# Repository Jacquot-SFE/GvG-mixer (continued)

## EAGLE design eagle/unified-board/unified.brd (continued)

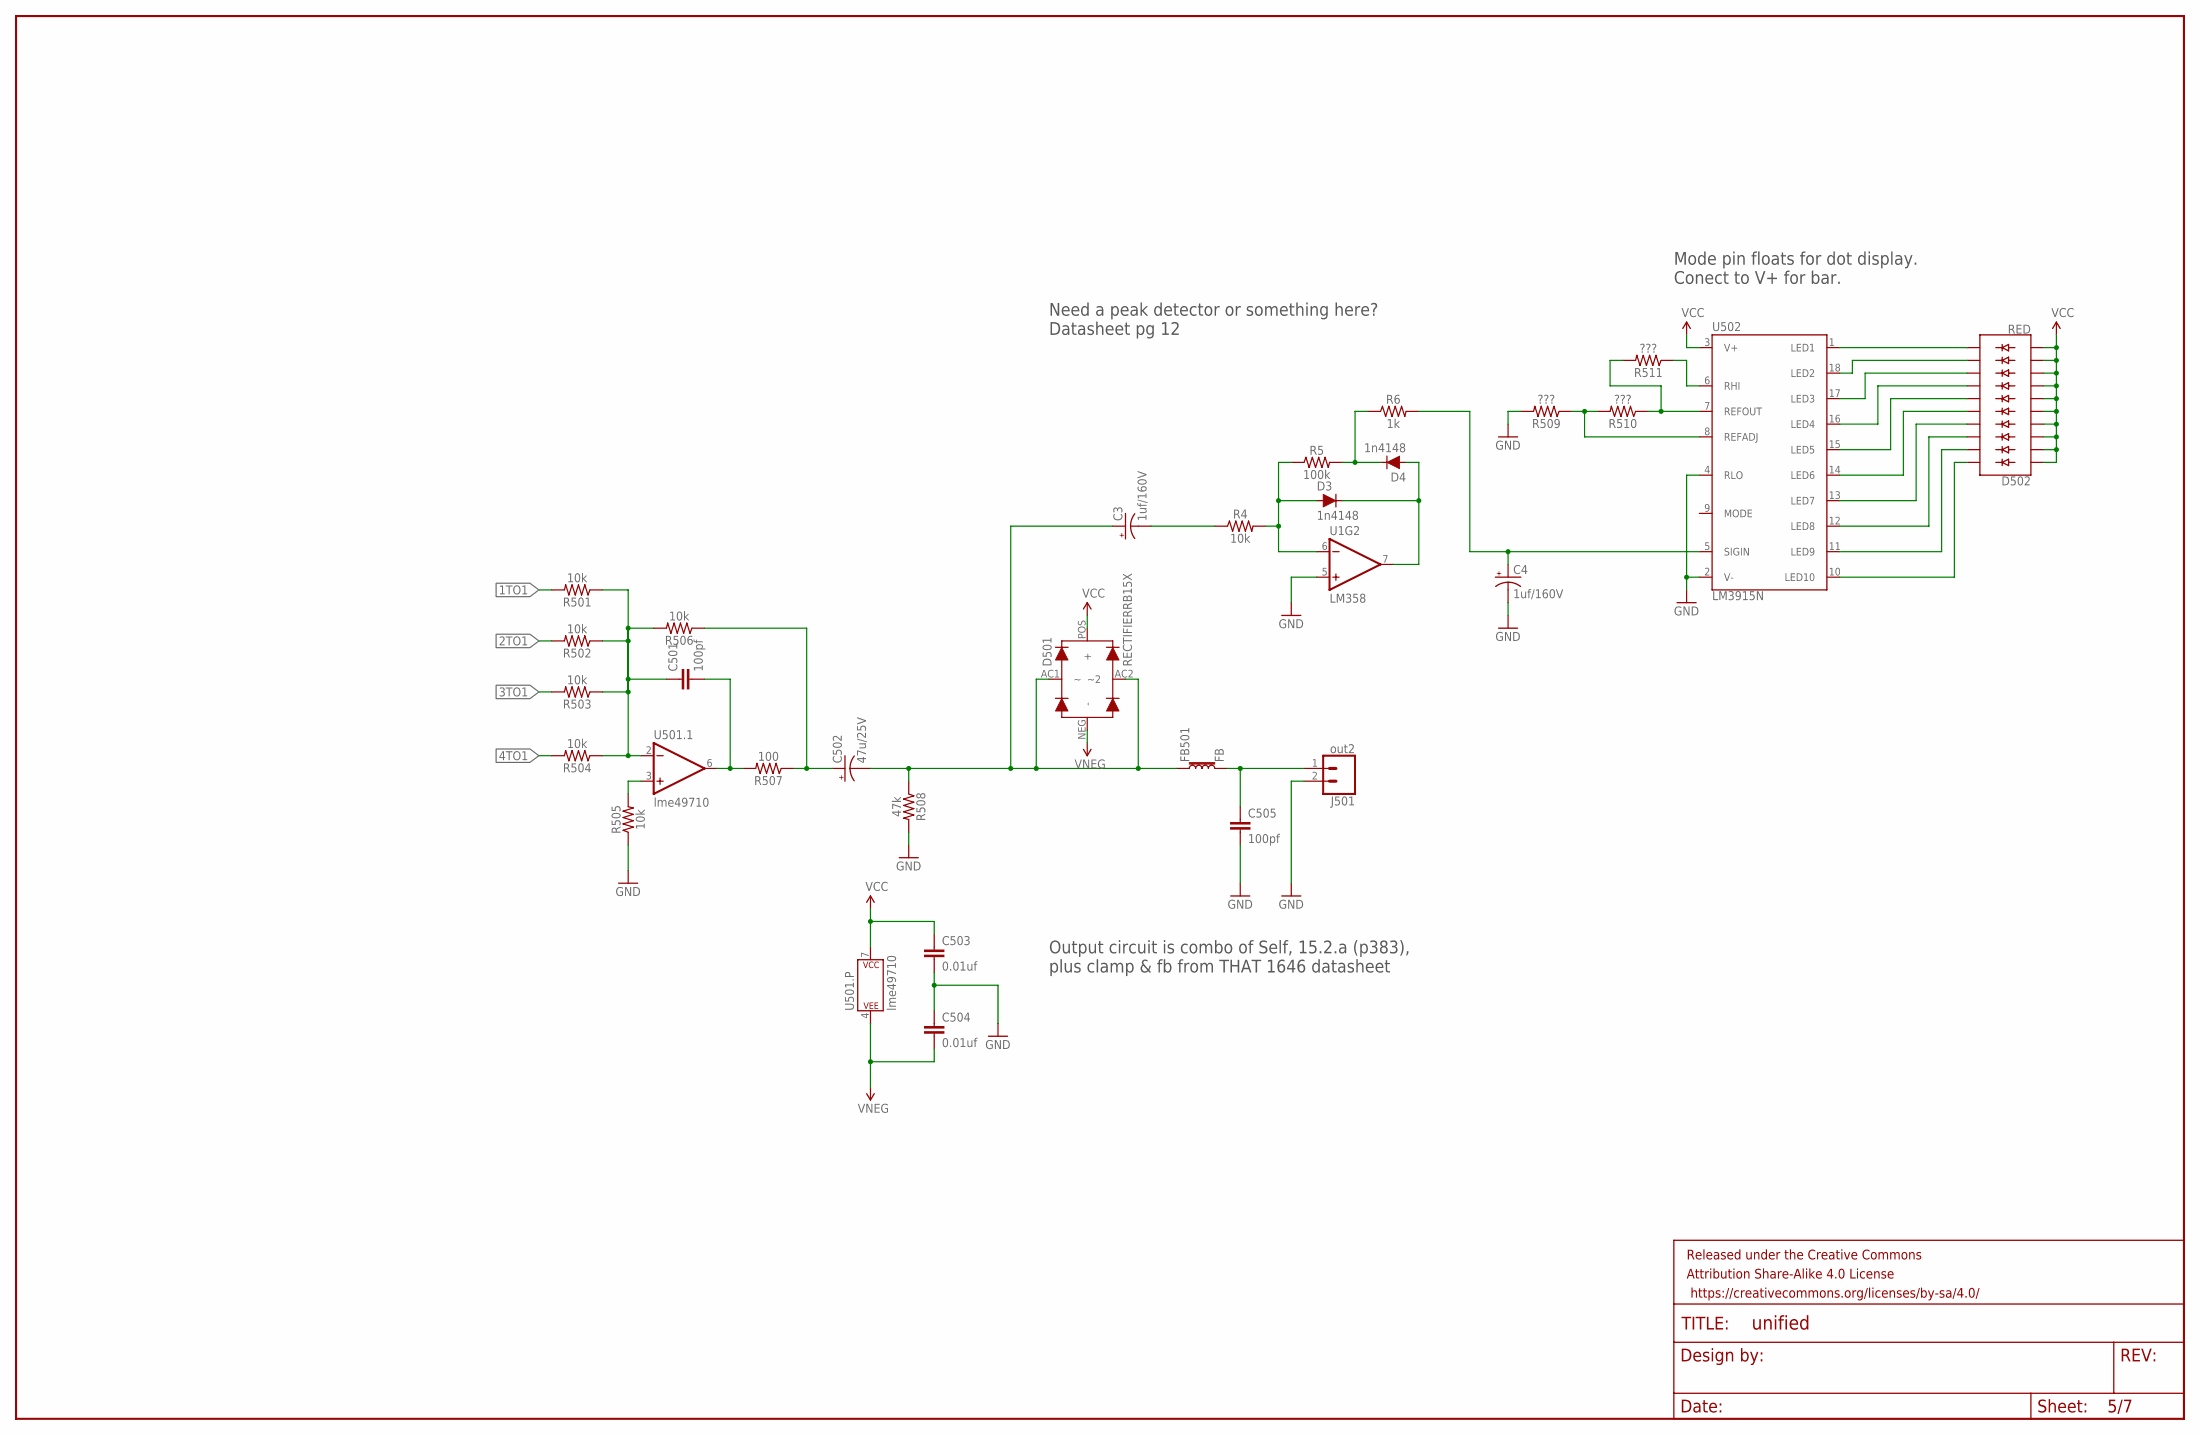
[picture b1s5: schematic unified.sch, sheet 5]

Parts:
C3, C4: 1uf/160V; CAP-PANA-2.5LS-6DIAM
C501, C505: 100pf; CAP-KEMET-GM-2.54LS
C502: 47u/25V; CAP-PANA-2LS-5DIAM
C503, C504: 0.01uf; WIMA-MKS2-2.5X7.2
D3, D4: 1n4148; DIODE-1N4148
D501: RECTIFIERRB15X; SM-RECTIFIER
D502: RED; LED_BARGRAPH_10
FB501: FB; BEAD
FRAME501: FRAME-LEDGER; CREATIVE_COMMONS
J501: out2; 1X02_LOCK_LONGPADS
R4, R501, R502, R503, R504, R505, R506: 10k; AXIAL-0.3
R5: 100k; AXIAL-0.3
R6: 1k; AXIAL-0.3
R507: 100; AXIAL-0.3
R508: 47k; AXIAL-0.3
R509, R510, R511: ???; AXIAL-0.3
U1: LM358; DIP08
U501: lme49710; DIP08-KIT
U502: LM3915N; DIL18

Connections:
1TO1: R501.P$2 (2); also elsewhere on the board
2TO1: R502.P$2 (2); also elsewhere on the board
3TO1: R503.P$2 (2); also elsewhere on the board
4TO1: R504.P$2 (2); also elsewhere on the board
GND: C4.NEG (-), C503.P$2 (2), C504.P$1 (1), C505.P$2 (2), J501.2, R505.P$1 (1), R508.P$2 (2), R509.P$2 (2), U1.5 (+IN), U502.2 (V-), U502.4 (RLO); also elsewhere on the board
HIGHEST1: D502.20 (C), U502.10 (LED10)
LOWEST1: D502.11 (C9), U502.1 (LED1)
unnamed: D3.A, R4.P$2 (2), R5.P$1 (1), U1.6 (-IN)
unnamed: D3.C, D4.A, U1.7 (OUT)
unnamed: D4.C, R5.P$2 (2), R6.P$1 (1)
unnamed: C3.NEG (-), R4.P$1 (1)
unnamed: C4.POS (+), R6.P$2 (2), U502.5 (SIGIN)
unnamed: R505.P$2 (2), U501.3 (+IN)
unnamed: C501.P$1 (1), R501.P$1 (1), R502.P$1 (1), R503.P$1 (1), R504.P$1 (1), R506.P$2 (2), U501.2 (-IN)
unnamed: C505.P$1 (1), FB501.P$2 (2), J501.1
unnamed: C3.POS (+), C502.NEG (-), D501.AC1, D501.AC2 (~2), FB501.P$1 (1), R508.P$1 (1)
unnamed: D502.12 (C8), U502.18 (LED2)
unnamed: D502.13 (C7), U502.17 (LED3)
unnamed: D502.14 (C6), U502.16 (LED4)
unnamed: D502.15 (C5), U502.15 (LED5)
unnamed: D502.16 (C4), U502.14 (LED6)
unnamed: D502.17 (C3), U502.13 (LED7)
unnamed: D502.18 (C2), U502.12 (LED8)
unnamed: D502.19 (C1), U502.11 (LED9)
unnamed: R510.P$1 (1), R511.P$2 (2), U502.7 (REFOUT)
unnamed: R509.P$1 (1), R510.P$2 (2), U502.8 (REFADJ)
unnamed: C501.P$2 (2), R507.P$2 (2), U501.6 (OUT)
unnamed: C502.POS (+), R506.P$1 (1), R507.P$1 (1)
unnamed: R511.P$1 (1), U502.6 (RHI)
VCC: C503.P$1 (1), D501.POS (+), D502.1 (A), D502.2 (A1), D502.3 (A2), D502.4 (A3), D502.5 (A4), D502.6 (A5), D502.7 (A6), D502.8 (A7), D502.9 (A8), D502.10 (A9), U501.7 (P$V+), U502.3 (V+); also elsewhere on the board
VNEG: C504.P$2 (2), D501.NEG (-), U501.4 (P$V-); also elsewhere on the board

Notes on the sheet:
Need a peak detector or something here? Datasheet pg 12
Mode pin floats for dot display. Conect to V+ for bar.
Output circuit is combo of Self, 15.2.a (p383), plus clamp & fb from THAT 1646 datasheet

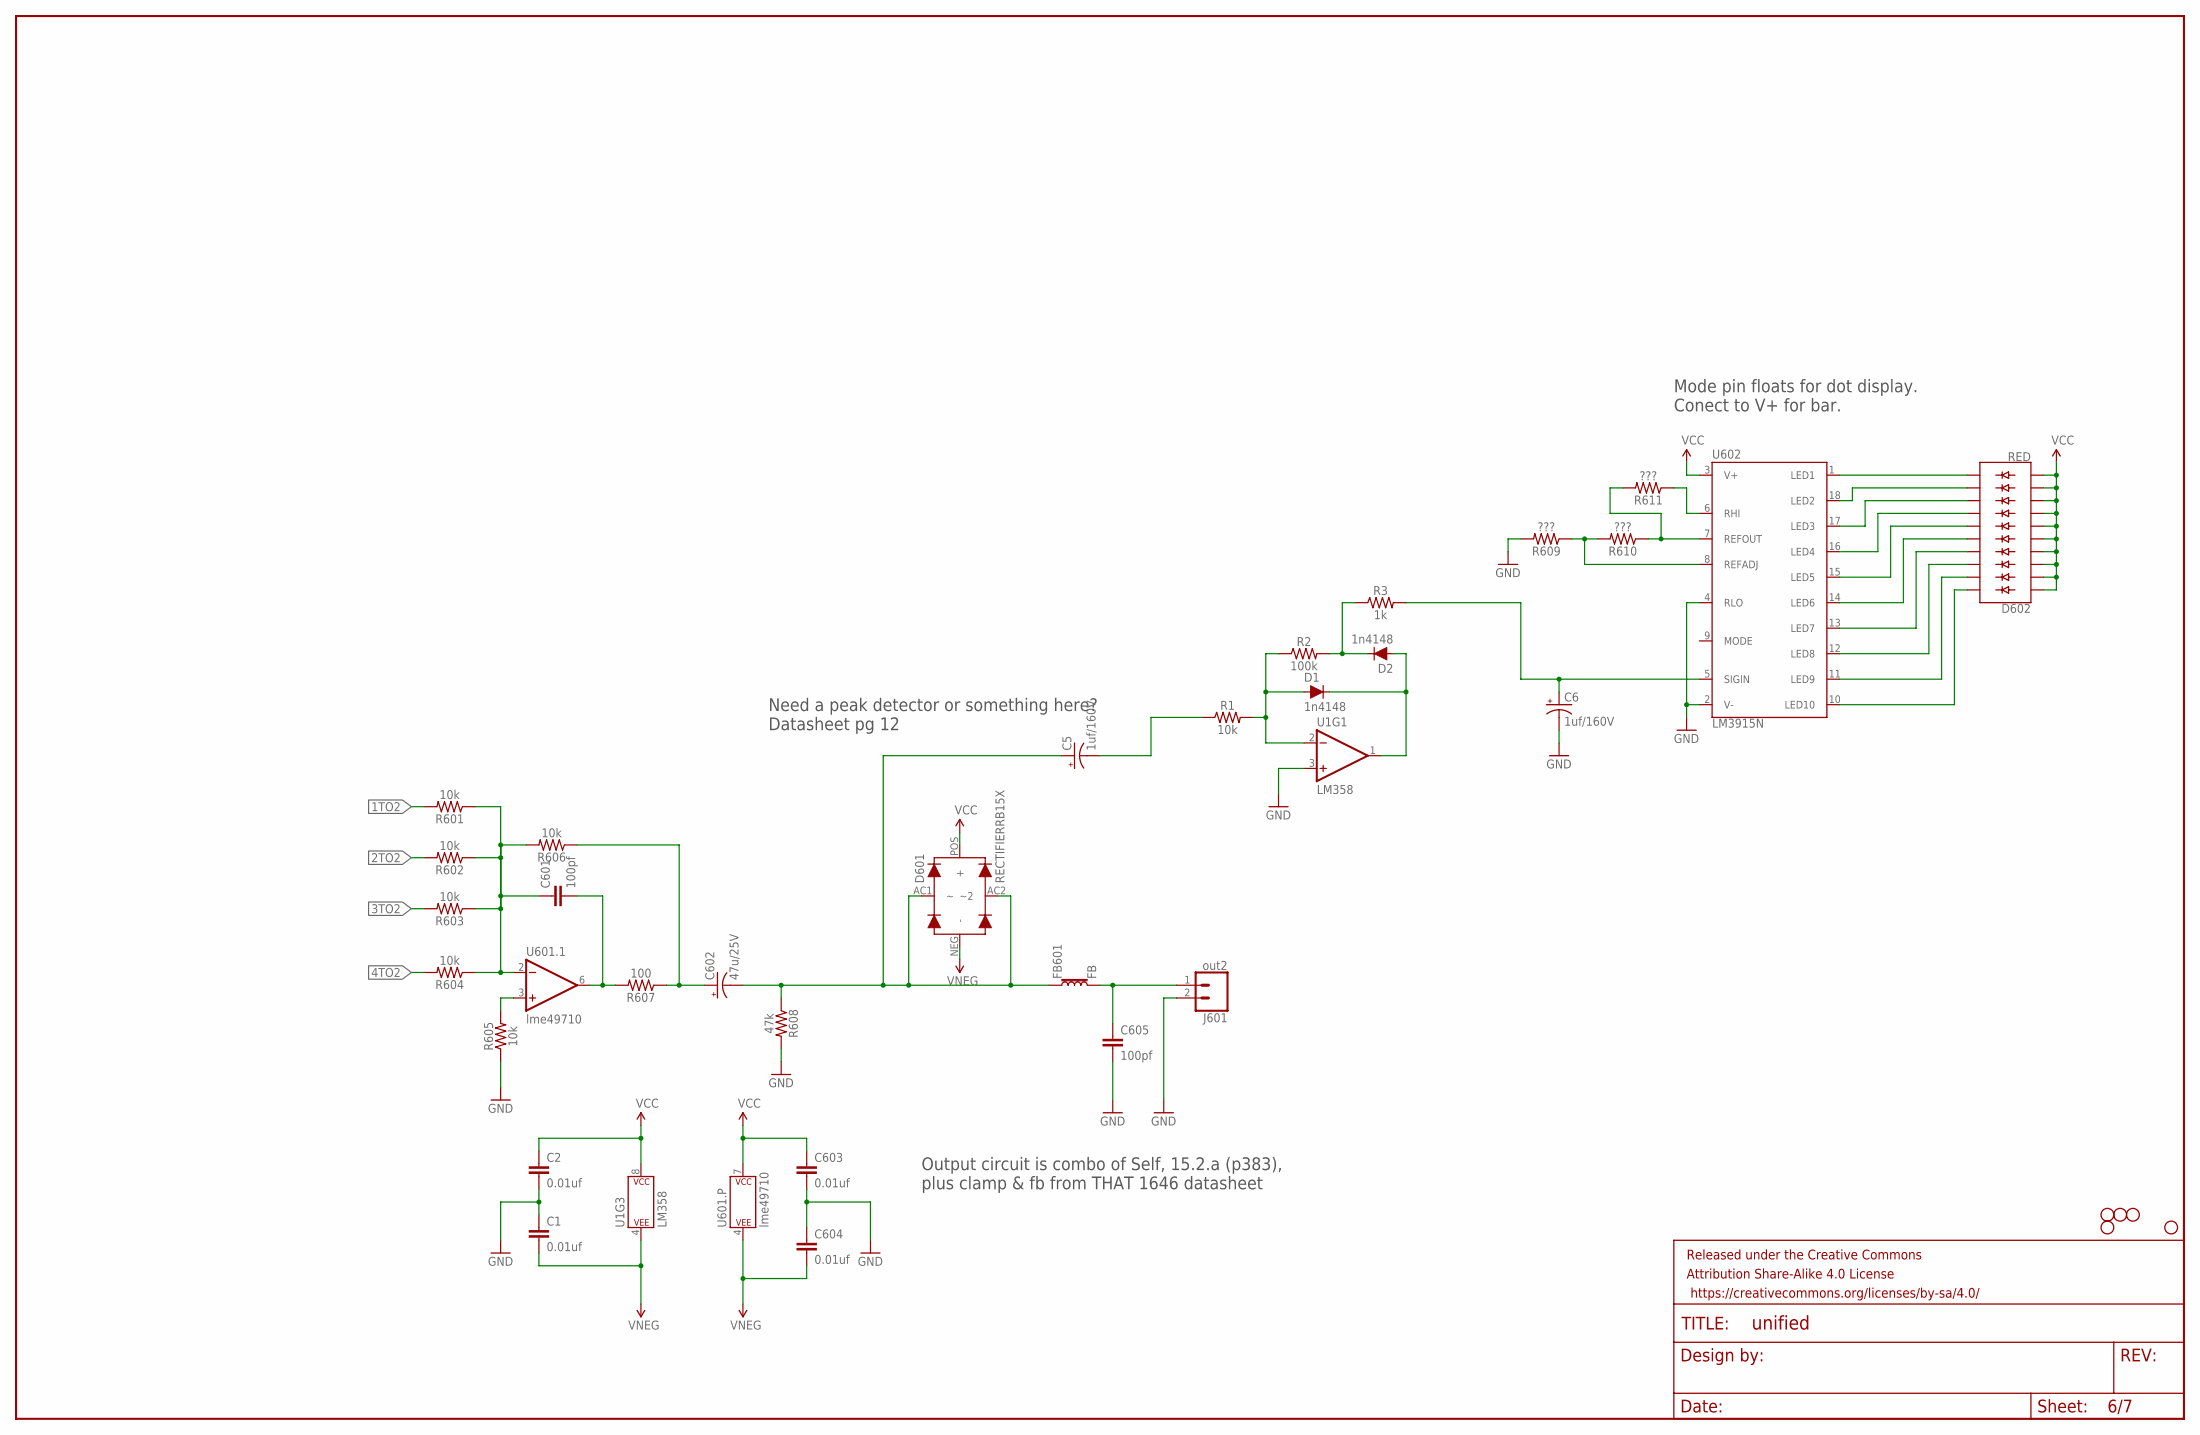
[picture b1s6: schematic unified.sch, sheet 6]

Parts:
C1, C2, C603, C604: 0.01uf; WIMA-MKS2-2.5X7.2
C5, C6: 1uf/160V; CAP-PANA-2.5LS-6DIAM
C601, C605: 100pf; CAP-KEMET-GM-2.54LS
C602: 47u/25V; CAP-PANA-2LS-5DIAM
D1, D2: 1n4148; DIODE-1N4148
D601: RECTIFIERRB15X; SM-RECTIFIER
D602: RED; LED_BARGRAPH_10
FB601: FB; BEAD
FRAME601: FRAME-LEDGER; CREATIVE_COMMONS
H601, H602, H603, H605, H612: STAND-OFF
J601: out2; 1X02_LOCK_LONGPADS
R1, R601, R602, R603, R604, R605, R606: 10k; AXIAL-0.3
R2: 100k; AXIAL-0.3
R3: 1k; AXIAL-0.3
R607: 100; AXIAL-0.3
R608: 47k; AXIAL-0.3
R609, R610, R611: ???; AXIAL-0.3
U1: LM358; DIP08
U601: lme49710; DIP08-KIT
U602: LM3915N; DIL18

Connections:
1TO2: R601.P$2 (2); also elsewhere on the board
2TO2: R602.P$2 (2); also elsewhere on the board
3TO2: R603.P$2 (2); also elsewhere on the board
4TO2: R604.P$2 (2); also elsewhere on the board
GND: C1.P$1 (1), C2.P$2 (2), C6.NEG (-), C603.P$2 (2), C604.P$1 (1), C605.P$2 (2), J601.2, R605.P$1 (1), R608.P$2 (2), R609.P$2 (2), U1.3 (+IN), U602.2 (V-), U602.4 (RLO); also elsewhere on the board
HIGHEST: D602.20 (C), U602.10 (LED10)
LOWEST: D602.11 (C9), U602.1 (LED1)
unnamed: D1.A, R1.P$2 (2), R2.P$1 (1), U1.2 (-IN)
unnamed: C605.P$1 (1), FB601.P$2 (2), J601.1
unnamed: D1.C, D2.A, U1.1 (OUT)
unnamed: C5.POS (+), C602.NEG (-), D601.AC1, D601.AC2 (~2), FB601.P$1 (1), R608.P$1 (1)
unnamed: C602.POS (+), R606.P$1 (1), R607.P$1 (1)
unnamed: R605.P$2 (2), U601.3 (+IN)
unnamed: C601.P$2 (2), R607.P$2 (2), U601.6 (OUT)
unnamed: C601.P$1 (1), R601.P$1 (1), R602.P$1 (1), R603.P$1 (1), R604.P$1 (1), R606.P$2 (2), U601.2 (-IN)
unnamed: D2.C, R2.P$2 (2), R3.P$1 (1)
unnamed: C6.POS (+), R3.P$2 (2), U602.5 (SIGIN)
unnamed: D602.12 (C8), U602.18 (LED2)
unnamed: D602.13 (C7), U602.17 (LED3)
unnamed: D602.14 (C6), U602.16 (LED4)
unnamed: D602.15 (C5), U602.15 (LED5)
unnamed: D602.16 (C4), U602.14 (LED6)
unnamed: D602.17 (C3), U602.13 (LED7)
unnamed: D602.18 (C2), U602.12 (LED8)
unnamed: D602.19 (C1), U602.11 (LED9)
unnamed: R610.P$1 (1), R611.P$2 (2), U602.7 (REFOUT)
unnamed: R609.P$1 (1), R610.P$2 (2), U602.8 (REFADJ)
unnamed: R611.P$1 (1), U602.6 (RHI)
unnamed: C5.NEG (-), R1.P$1 (1)
VCC: C2.P$1 (1), C603.P$1 (1), D601.POS (+), D602.1 (A), D602.2 (A1), D602.3 (A2), D602.4 (A3), D602.5 (A4), D602.6 (A5), D602.7 (A6), D602.8 (A7), D602.9 (A8), D602.10 (A9), U1.8 (P$V+), U601.7 (P$V+), U602.3 (V+); also elsewhere on the board
VNEG: C1.P$2 (2), C604.P$2 (2), D601.NEG (-), U1.4 (P$V-), U601.4 (P$V-); also elsewhere on the board

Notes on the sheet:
Need a peak detector or something here? Datasheet pg 12
Mode pin floats for dot display. Conect to V+ for bar.
Output circuit is combo of Self, 15.2.a (p383), plus clamp & fb from THAT 1646 datasheet

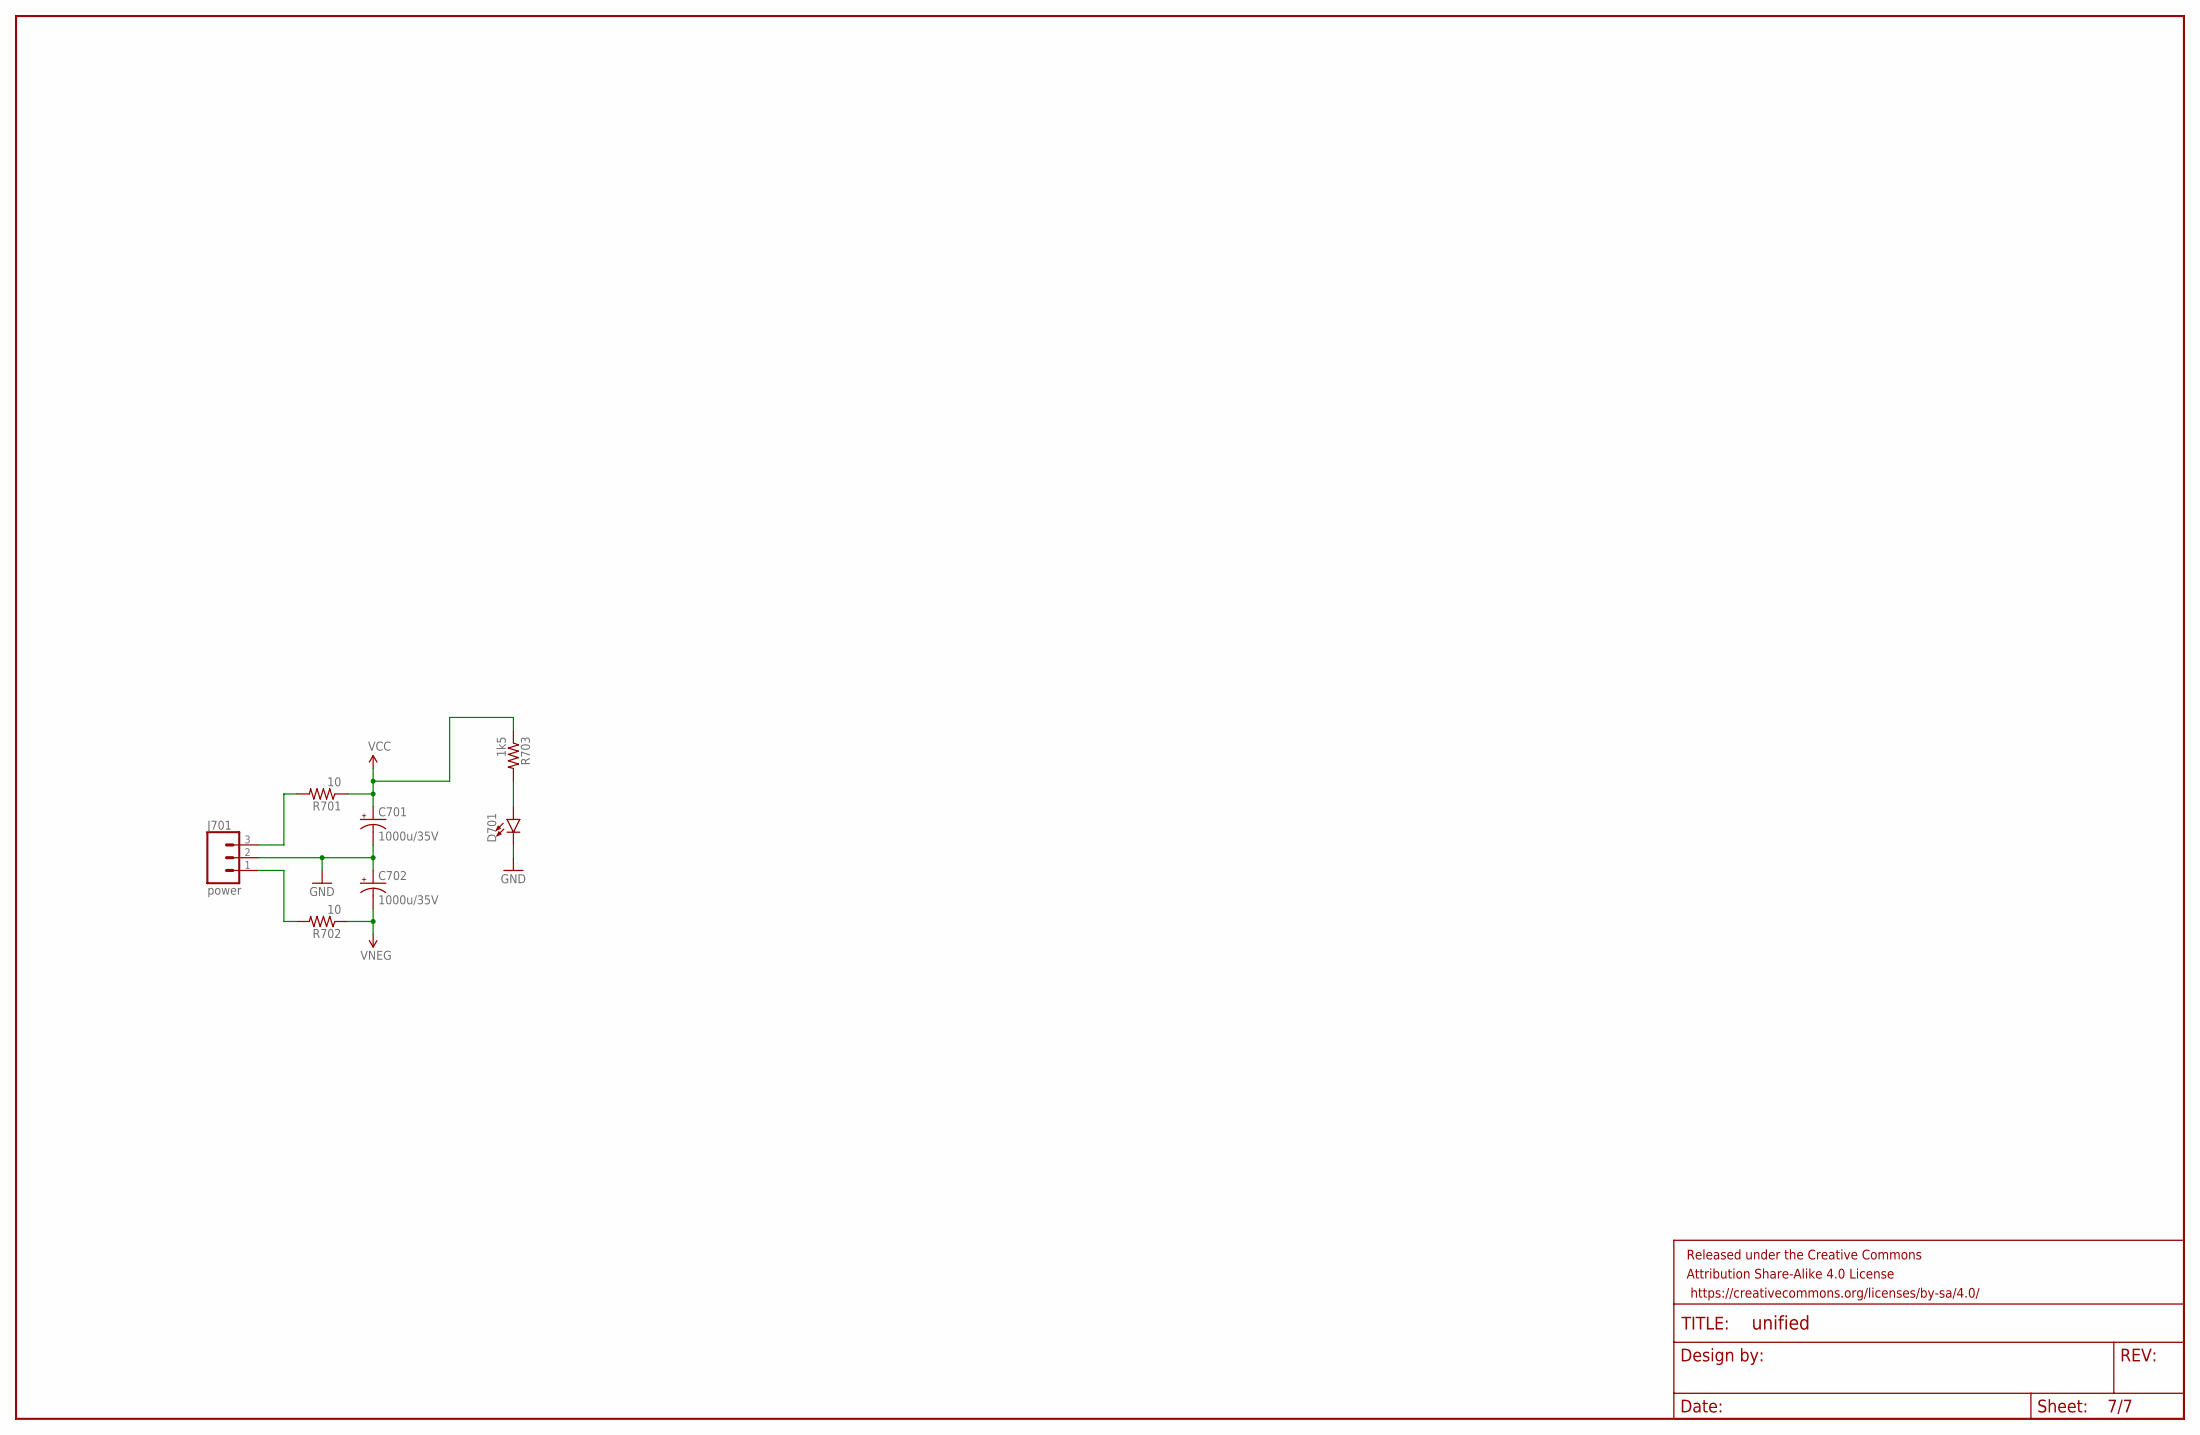
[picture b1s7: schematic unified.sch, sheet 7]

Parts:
C701, C702: 1000u/35V; CAP-PANA-5LS-12.5DIAM
D701: LED5MM; LED_5MM
FRAME701: FRAME-LEDGER; CREATIVE_COMMONS
J701: power; MOLEX-1X3_LOCK
R701, R702: 10; AXIAL-0.3
R703: 1k5; AXIAL-0.3

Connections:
GND: C701.NEG (-), C702.POS (+), D701.K (C), J701.2; also elsewhere on the board
unnamed: J701.1, R702.P$2 (2)
unnamed: J701.3, R701.P$2 (2)
unnamed: D701.A, R703.P$2 (2)
VCC: C701.POS (+), R701.P$1 (1), R703.P$1 (1); also elsewhere on the board
VNEG: C702.NEG (-), R702.P$1 (1); also elsewhere on the board

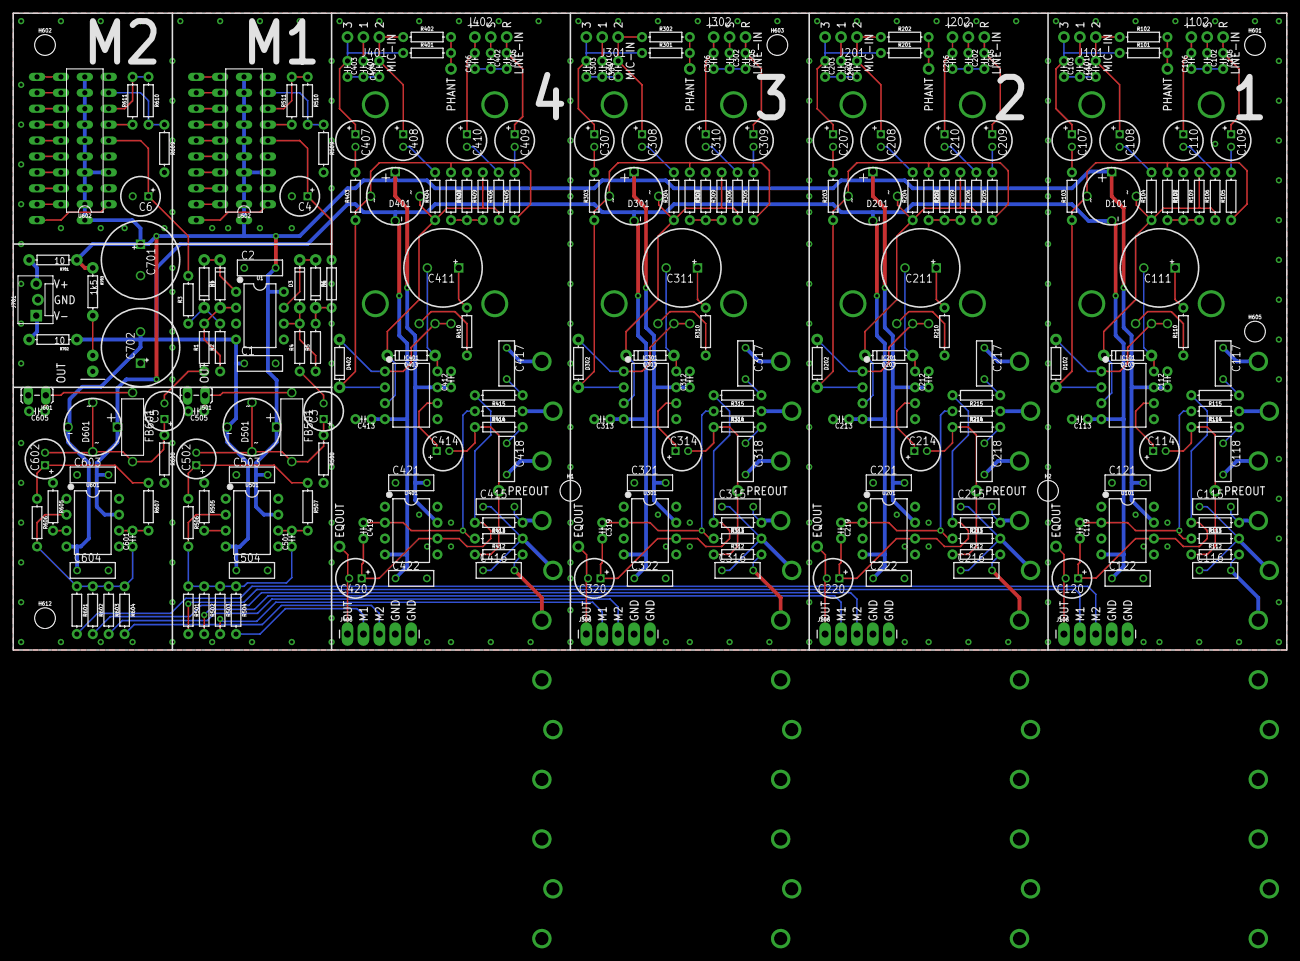
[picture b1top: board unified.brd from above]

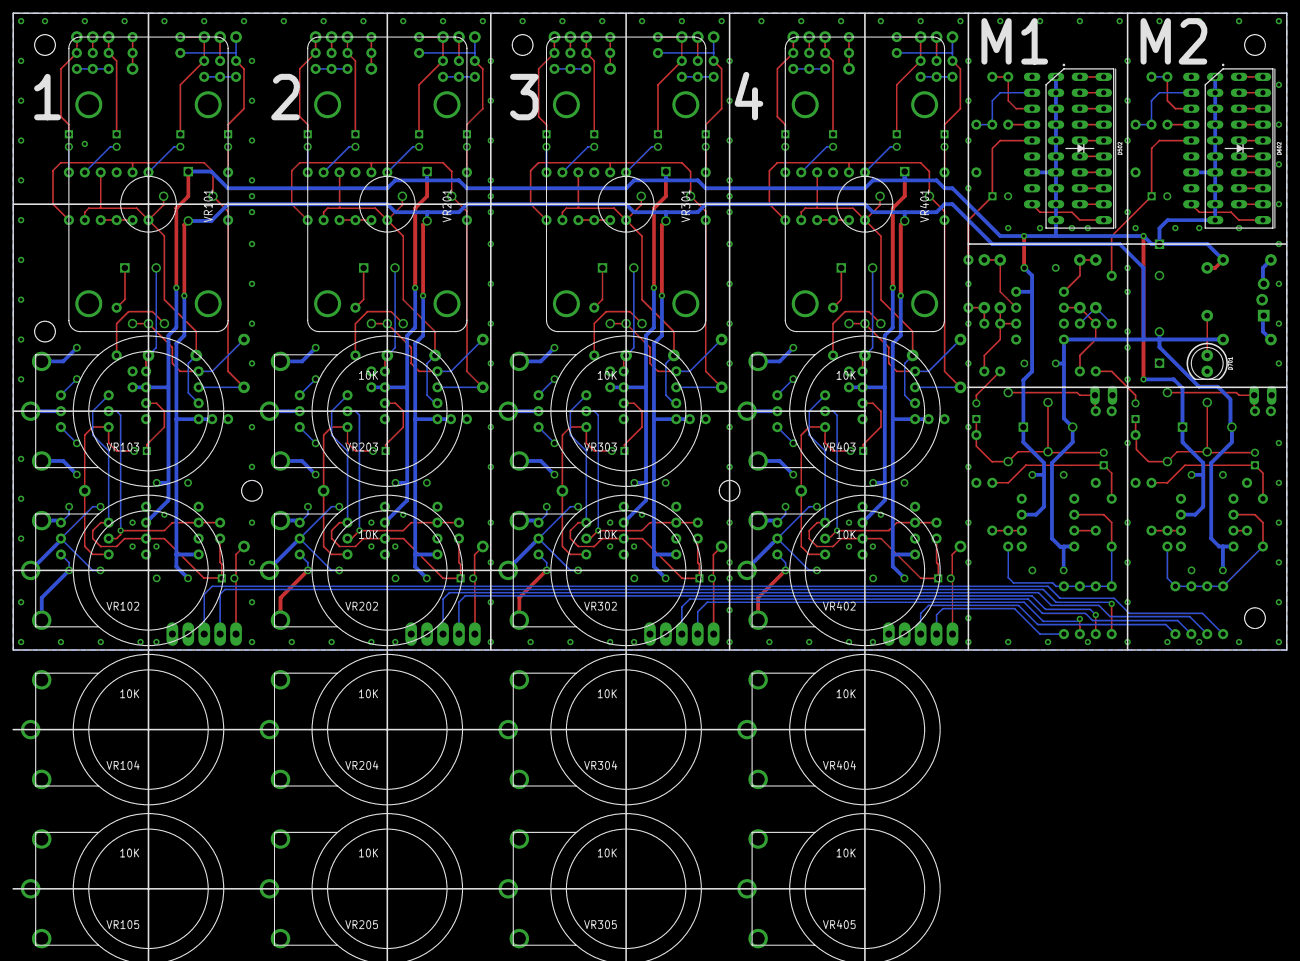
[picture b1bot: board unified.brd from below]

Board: 2 copper layers, 203.2 x 101.6 mm, 298 parts (23 on the bottom side), 194 nets.

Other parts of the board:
H1, H2: STAND-OFF

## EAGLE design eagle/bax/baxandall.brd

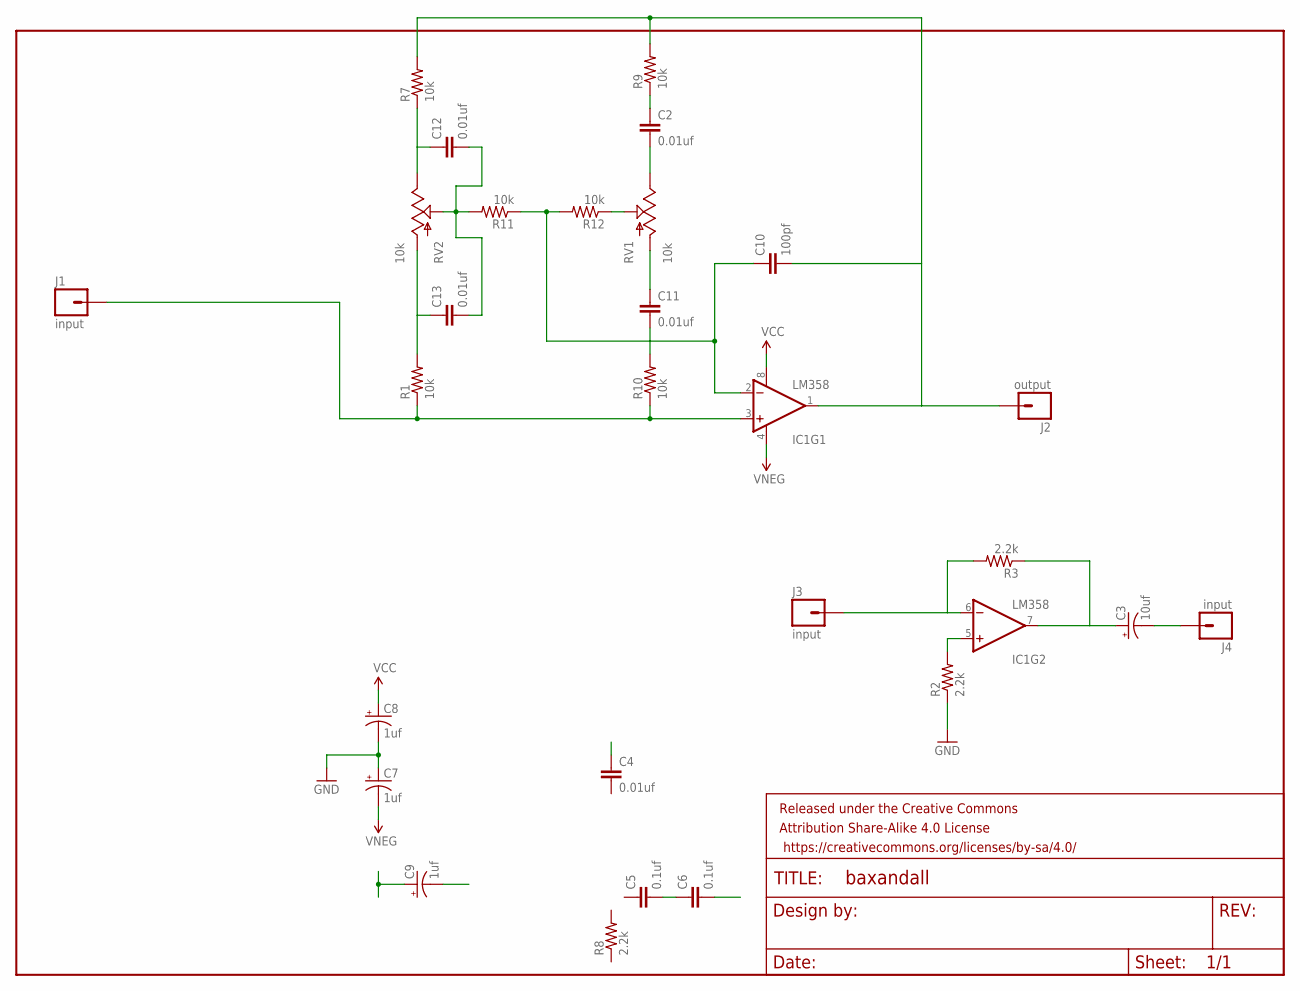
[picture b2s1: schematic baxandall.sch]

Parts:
C2, C4, C11, C12, C13: 0.01uf; CAP-PTH-SMALL
C3: 10uf; CPOL-RADIAL-10UF-25V
C5, C6: 0.1uf; CAP-PTH-SMALL
C7, C8, C9: 1uf; CPOL-RADIAL-10UF-25V
C10: 100pf; CAP-PTH-SMALL
FRAME1: FRAME-LETTER; CREATIVE_COMMONS
IC1: LM358; DIP08
J1, J3, J4: input; 1X01NS-KIT
J2: output; 1X01NS-KIT
R1, R7, R9, R10, R11, R12: 10k; AXIAL-0.3
R2, R3, R8: 2.2k; AXIAL-0.3
RV1, RV2: 10k; POT_ALPHA_RV16AF-20

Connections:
GND: C7.1 (+), C8.2 (-), R2.P$1 (1)
unnamed: C12.1, R7.P$1 (1), RV2.3 (E)
unnamed: C13.1, R1.P$2 (2), RV2.1 (A)
unnamed: C10.1, IC1.2 (-IN), R11.P$1 (1), R12.P$2 (2)
unnamed: C11.2, R10.P$2 (2)
unnamed: C10.2, IC1.1 (OUT), J2.1, R7.P$2 (2), R9.P$2 (2)
unnamed: IC1.5 (+IN), R2.P$2 (2)
unnamed: C3.1 (+), IC1.7 (OUT), R3.P$1 (1)
unnamed: R12.P$1 (1), RV1.2 (S)
unnamed: IC1.3 (+IN), J1.1, R1.P$1 (1), R10.P$1 (1)
unnamed: C11.1, RV1.1 (A)
unnamed: IC1.6 (-IN), J3.1, R3.P$2 (2)
unnamed: C3.2 (-), J4.1
unnamed: C12.2, C13.2, R11.P$2 (2), RV2.2 (S)
unnamed: C2.2, RV1.3 (E)
unnamed: C5.2, C6.1
unnamed: C2.1, R9.P$1 (1)
VCC: C8.1 (+), IC1.8 (V+)
VNEG: C7.2 (-), IC1.4 (V-)

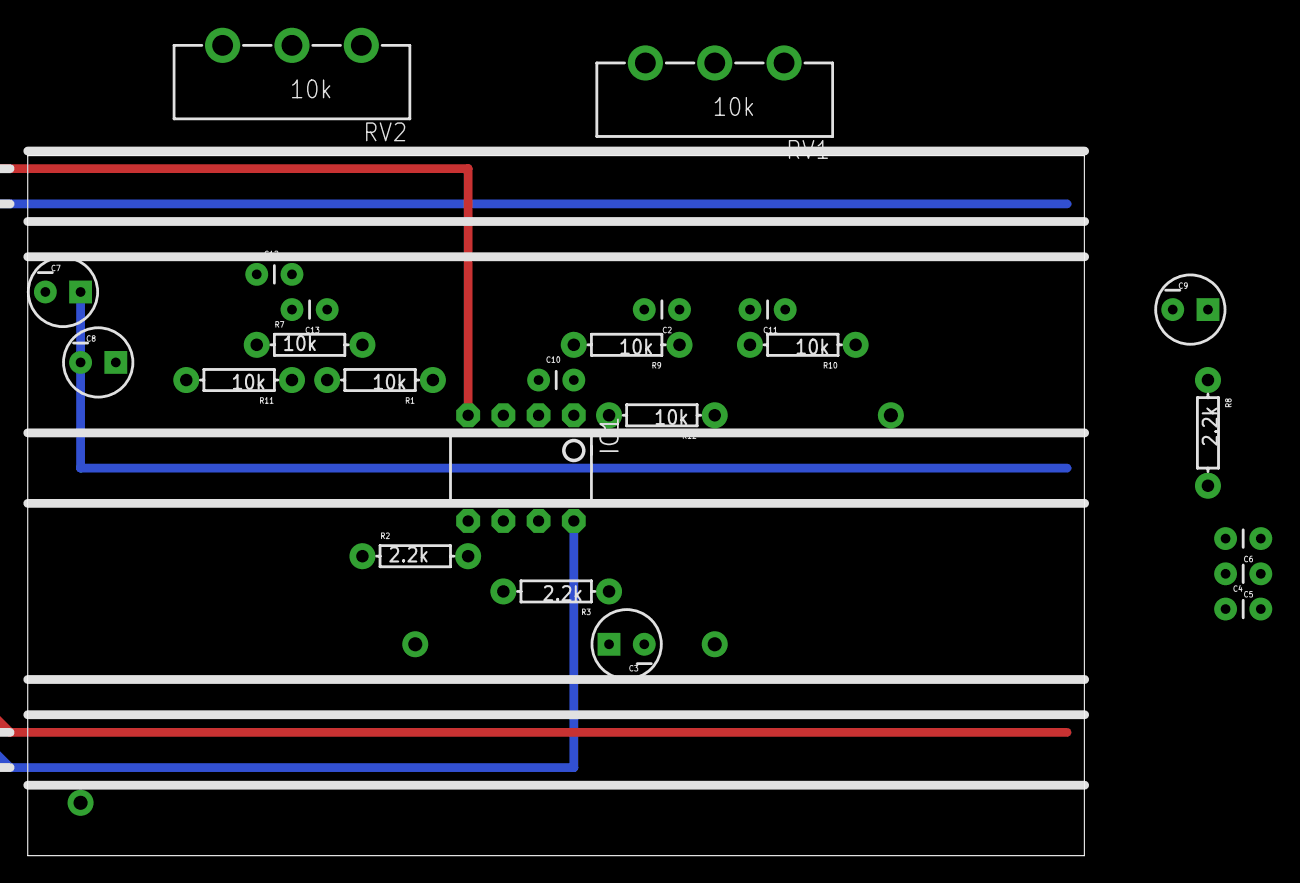
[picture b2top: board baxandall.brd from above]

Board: 2 copper layers, 29 parts (0 on the bottom side), 19 nets.

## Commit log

2016-12-16 first commit - attributes and ignore
2016-12-16 Adding initial commit of design files.
2016-12-16 Adding some SVG stuff.
2016-12-19 Moving to unified board design, adding datasheets.
2016-12-19 Added ferrite bead & datasheet
2016-12-20 A couple more bits done up.
2016-12-20 Some initial routing
    one input, one output, placeholders for more.
2016-12-20 A few tweaks.
    Forgot that it needs to run right-to-left.
    Added standoffs and some silk legending.
2016-12-22 Capacitor update
    sourced & created a bunch of caps.
    pushed components around more & better.
2016-12-23 Conforming parts on BOM for ordering.
    verified mouser & SFe part #s.
2016-12-24 Duplicated input channels.
2016-12-25 Assigning net classes, second summing channel.
2016-12-26 Channels routed...
2016-12-26 Keeping moving.
    Calculated preamp R-strings.
    Tried for the bargraphs...jusy is still out...
    Added peak tracker for meter circuit.
2016-12-30 Possibly complete?
    doublechecked all IC footprints.
    Routed the peak detector & found 1uf caps for it.
2017-01-02 More touchups.
    Doublechecked rotary switch direction and values.
    Added some dimension lines.
2017-01-04 Adding part numbers to some off-PCB parts.
2017-01-30 Adding unified BOM.
2017-01-30 Some updates.
    -More BOM detail
    -SVG for temp panel.
    -Few more dimensions on board.
    -Tweaking preamp gains on rotpot boards.
2017-02-10 Many changes from checkplots.
    Some footprints were incorrect. Library, board & schem all updated.
2017-02-11 Peppered the board with ground stitch vias.
2017-02-17 Board touchups before gerbers.
2017-03-17 Notes from assembly
    -Recalc'd preamp gains for actual resistors.
    -added panel SVG & PDF files.
2017-04-05 Removing dead-end design files, adding gerbers.
2017-04-06 Amended readme.
